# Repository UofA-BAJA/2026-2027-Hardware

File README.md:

# 2026-2027-Hardware

The repository of all hardware for 2026-2027 UofA Baja

Electrical Lead - Graham VanDerBeek

Software Lead - Karsten Yin

#### Projects:

Tachometer -

Speedometer -

Shock Displacement -

Brake Pressure -

GPS -

CVT Temp -

IMU -

Dash - Adam Esch
 HELLO

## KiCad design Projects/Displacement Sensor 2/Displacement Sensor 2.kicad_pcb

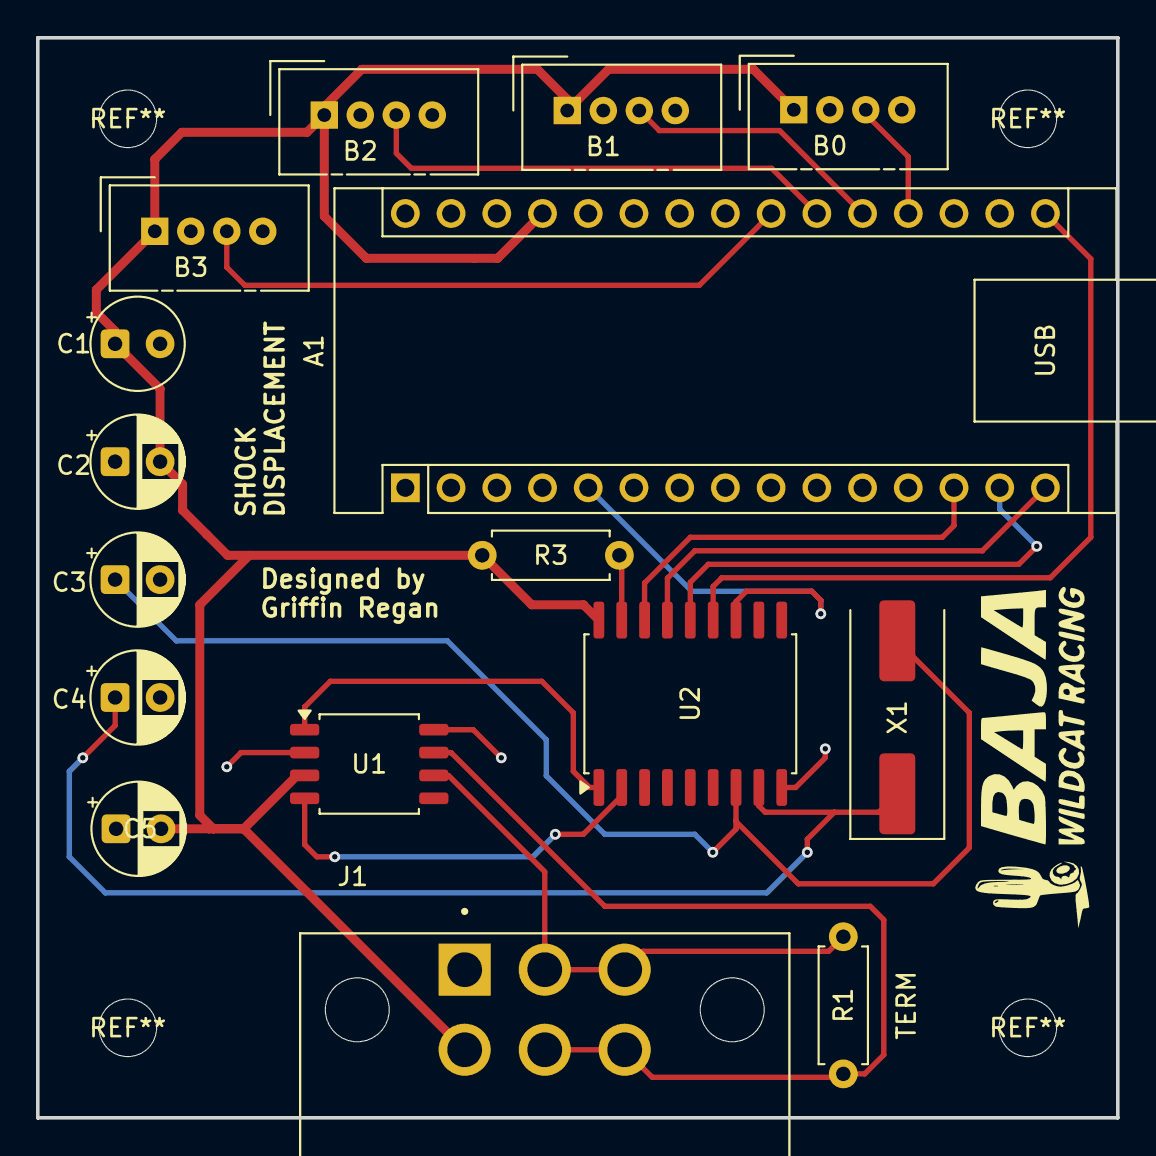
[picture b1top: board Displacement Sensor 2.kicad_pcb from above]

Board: 2 copper layers, 60.0 x 60.0 mm, 16 parts (0 on the bottom side), 18 nets.

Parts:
A1: Arduino_Nano_v3.x; Arduino_Nano
B0, B1, B2, B3: NS-Tech_Grove_1x04_P2mm_Vertical
C1: 10uF/16V; CP_Radial_Tantal_D5.0mm_P2.50mm
C2, C5: 100nF; CP_Radial_D5.0mm_P2.50mm
C3, C4: 22pF; CP_Radial_D5.0mm_P2.50mm
J1: DTF13-6P; TE_DTF13-6P
R1: TERM; R_Axial_DIN0207_L6.3mm_D2.5mm_P7.62mm_Horizontal
R3: 10k; R_Axial_DIN0207_L6.3mm_D2.5mm_P7.62mm_Horizontal
U1: TJA1050DRG; SOIC-8_5.3x5.3mm_P1.27mm
U2: MCP2515-I; SOIC-18W_7.5x11.6mm_P1.27mm
X1: 8MHz; Crystal_SMD_HC49-SD

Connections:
+5V: A1.27 (+5V), B0.1 (5V), B1.1 (5V), B2.1 (5V), B3.1 (5V), C1.1, C2.2, C5.2, J1.6, R3.1, U1.3 (VCC), U2.18 (VDD)
CS: A1.13 (D10), U2.16 (~CS)
GND: A1.4 (GND), A1.29 (GND), B0.2 (GND), B0.4 (CGND), B1.2 (GND), B1.4 (CGND), B2.2 (GND), B2.4 (CGND), B3.2 (GND), B3.4 (CGND), C1.2, C2.1, C3.2, C4.2, C5.1, J1.1, U1.2 (GND), U1.8 (STB), U2.9 (VSS)
High: J1.4, J1.5, R1.2, U1.7 (CANH)
INT: A1.5 (D2), U2.12 (~INT)
Low: J1.2, J1.3, R1.1, U1.6 (CANL)
unnamed: A1.19 (A0), B0.3 (SIGNAL)
unnamed: A1.20 (A1), B1.3 (SIGNAL)
unnamed: A1.21 (A2), B2.3 (SIGNAL)
unnamed: A1.22 (A3), B3.3 (SIGNAL)
unnamed: U1.4 (RXD), U2.2 (RXCAN)
unnamed: U1.1 (TXD), U2.1 (TXCAN)
unnamed: C4.1, U2.8 (OSC1), X1.1
unnamed: C3.1, U2.7 (OSC2), X1.2
unnamed: R3.2, U2.17 (~RESET)
SCK: A1.16 (D13), U2.13 (SCK)
SI: A1.14 (D11), U2.14 (SI)
SO: A1.15 (D12), U2.15 (SO)

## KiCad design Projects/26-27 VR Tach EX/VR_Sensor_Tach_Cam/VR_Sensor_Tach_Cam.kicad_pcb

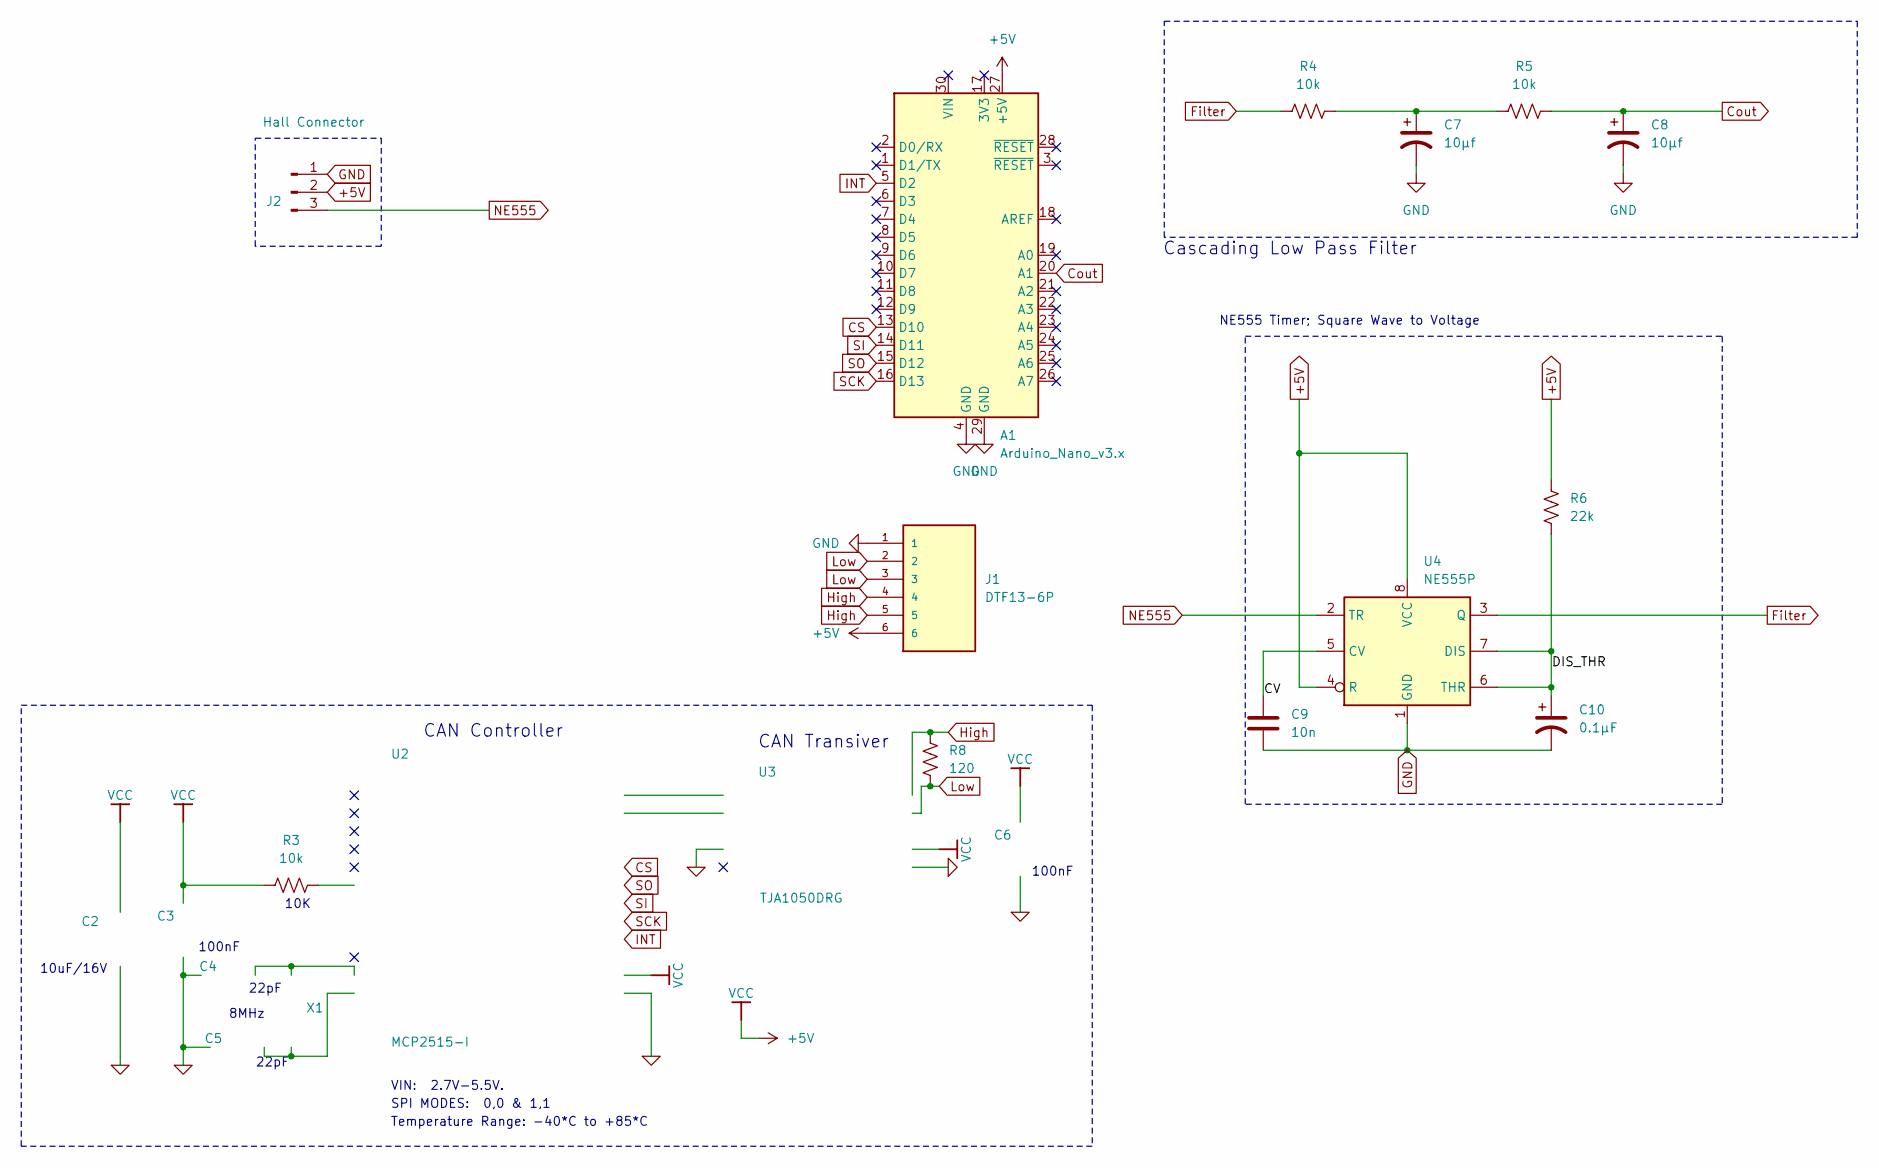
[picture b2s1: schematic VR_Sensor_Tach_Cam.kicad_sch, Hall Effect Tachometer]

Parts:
A1: Arduino_Nano_v3.x; Arduino_Nano
C2: 10uF/16V; CP_Radial_Tantal_D5.0mm_P2.50mm
C3, C6: 100nF; CP_Radial_D5.0mm_P2.50mm; PART NUMBER C0603-N.C.
C4, C5: 22pF; CP_Radial_D5.0mm_P2.50mm; PART NUMBER C0603-N.C.
C7, C8: 10μf; CP_Radial_D5.0mm_P2.50mm
C9: 10n; C_Disc_D3.8mm_W2.6mm_P2.50mm
C10: 0.1µF; CP_Radial_D6.3mm_P2.50mm
J1: DTF13-6P; TE_DTF13-6P; PARTREV B
J2: Hall Connector; SolderWire-2.5sqmm_1x03_P7.2mm_D2.4mm_OD3.6mm
R3, R4, R5: 10k; R_Axial_DIN0207_L6.3mm_D2.5mm_P10.16mm_Horizontal
R6: 22k; R_Axial_DIN0207_L6.3mm_D2.5mm_P10.16mm_Horizontal
R8: 120; R_Axial_DIN0207_L6.3mm_D2.5mm_P10.16mm_Horizontal
U2: MCP2515-I; SOIC-18W_7.5x11.6mm_P1.27mm; MANUFACTURER PART MCP2515-I; JLCPCB PART CLASS Extended Part
U3: TJA1050DRG; SOIC-8_5.3x5.3mm_P1.27mm; MANUFACTURER PART TJA1050DRG; LCSC PART NAME TJA1050DRG
U4: NE555P; DIP-8_W7.62mm
X1: 8MHz; Crystal_SMD_HC49-SD

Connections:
+5V: A1.27 (+5V), C2.1, C3.2, C6.2, J1.6, J2.2, R3.1, R6.1, U2.18 (VDD), U3.3 (VCC), U4.4 (R), U4.8 (VCC)
/CV: C9.2, U4.5 (CV)
/DIS_THR: C10.1, R6.2, U4.6 (THR), U4.7 (DIS)
CS: A1.13 (D10), U2.16 (~CS)
Cout: A1.20 (A1), C8.1, R5.1
Filter: R4.2, U4.3 (Q)
GND: A1.4 (GND), A1.29 (GND), C2.2, C3.1, C4.2, C5.2, C6.1, C7.2, C8.2, C9.1, C10.2, J1.1, J2.1, U2.9 (VSS), U3.2 (GND), U3.8 (STB), U4.1 (GND)
High: J1.4, J1.5, R8.1, U3.7 (CANH)
INT: A1.5 (D2), U2.12 (~INT)
Low: J1.2, J1.3, R8.2, U3.6 (CANL)
NE555: J2.3, U4.2 (TR)
unnamed: C7.1, R4.1, R5.2
unnamed: C5.1, U2.8 (OSC1), X1.1
unnamed: C4.1, U2.7 (OSC2), X1.2
unnamed: U2.2 (RXCAN), U3.4 (RXD)
unnamed: U2.1 (TXCAN), U3.1 (TXD)
unnamed: R3.2, U2.17 (~RESET)
SCK: A1.16 (D13), U2.13 (SCK)
SI: A1.14 (D11), U2.14 (SI)
SO: A1.15 (D12), U2.15 (SO)

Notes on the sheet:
VIN: 2.7V-5.5V.
8MHz
Cascading Low Pass Filter
10uF/16V
100nF
SPI MODES: 0,0 & 1,1
CAN Controller
CAN Transiver
10K
22pF
NE555 Timer; Square Wave to Voltage
Temperature Range: -40*C to +85*C

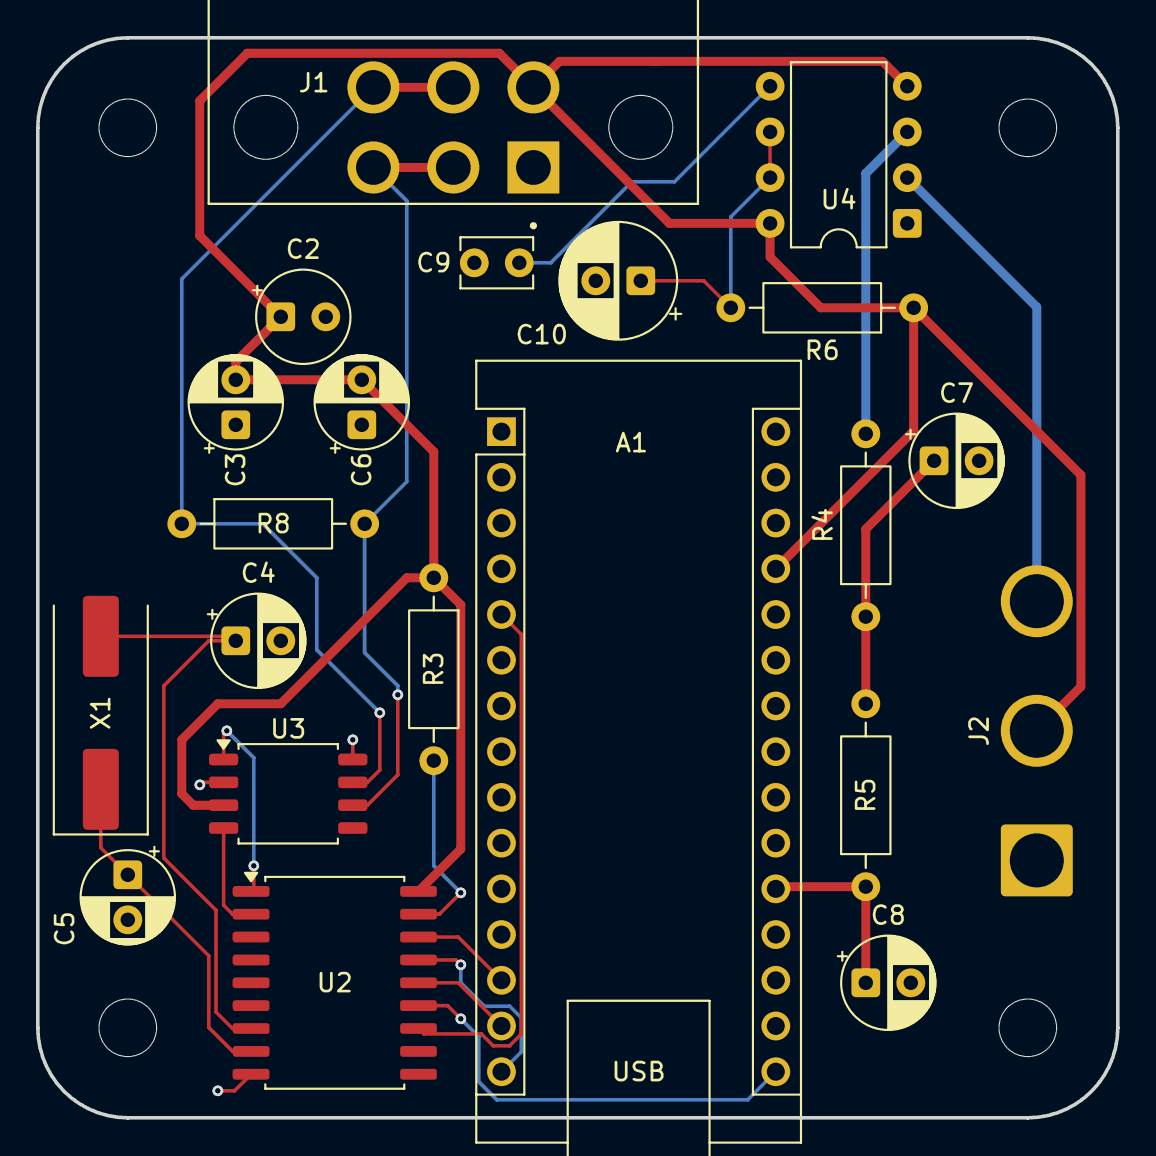
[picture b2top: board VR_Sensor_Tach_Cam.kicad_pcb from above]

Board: 2 copper layers, 60.0 x 60.0 mm, 21 parts (0 on the bottom side), 20 nets.

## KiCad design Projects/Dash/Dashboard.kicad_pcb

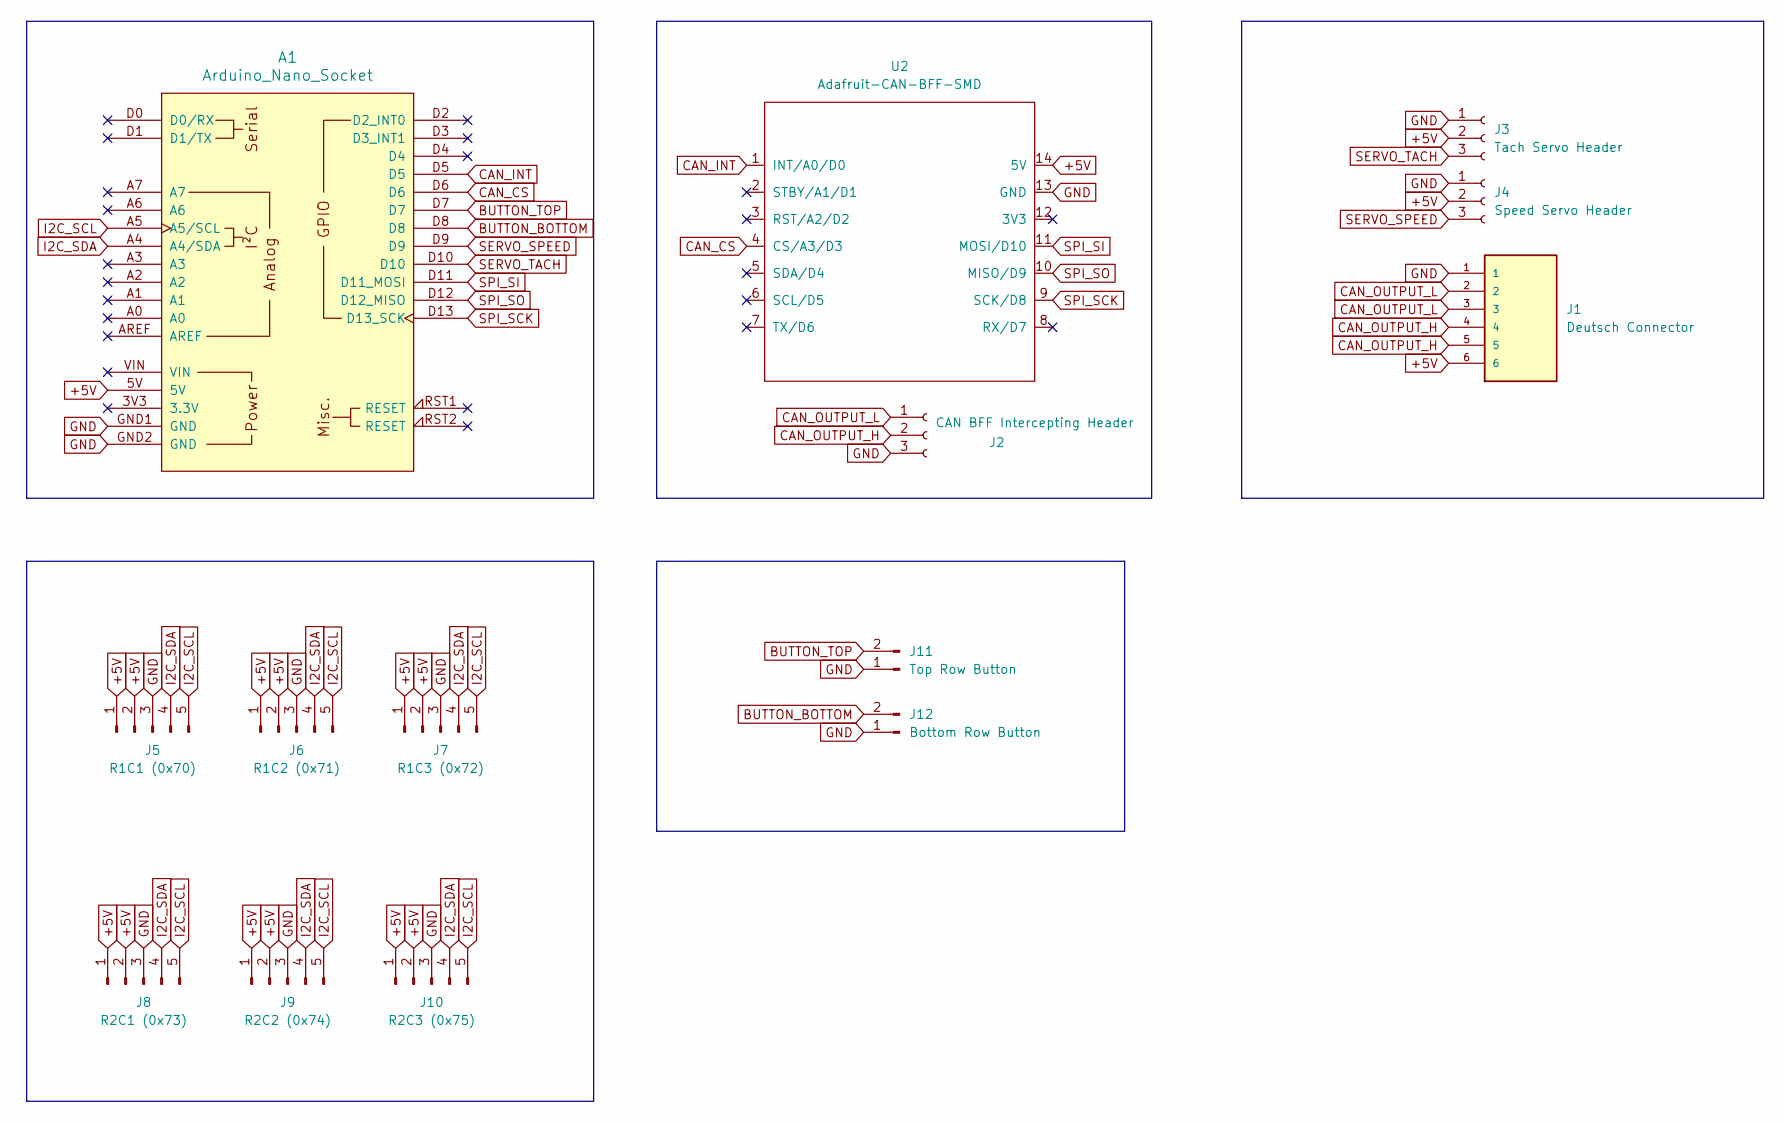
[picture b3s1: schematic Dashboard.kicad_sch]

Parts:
A1: Arduino_Nano_Socket
J1: Deutsch Connector; TE_DTF13-6P; PARTREV B
J2: CAN BFF Intercepting Header; PinHeader_1x03_P2.54mm_Vertical
J3: Tach Servo Header; PinHeader_1x03_P2.54mm_Vertical
J4: Speed Servo Header; PinHeader_1x03_P2.54mm_Vertical
J5: R1C1 (0x70); PinHeader_1x05_P2.54mm_Vertical
J6: R1C2 (0x71); PinHeader_1x05_P2.54mm_Vertical
J7: R1C3 (0x72); PinHeader_1x05_P2.54mm_Vertical
J8: R2C1 (0x73); PinHeader_1x05_P2.54mm_Vertical
J9: R2C2 (0x74); PinHeader_1x05_P2.54mm_Vertical
J10: R2C3 (0x75); PinHeader_1x05_P2.54mm_Vertical
J11: Top Row Button; PinHeader_1x02_P2.54mm_Vertical
J12: Bottom Row Button; PinHeader_1x02_P2.54mm_Vertical
U2: Adafruit-CAN-BFF-SMD

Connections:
+5V: A1.5V, J1.6, J3.2, J4.2, J5.1, J5.2, J6.1, J6.2, J7.1, J7.2, J8.1, J8.2, J9.1, J9.2, J10.1, J10.2, U2.14 (5V)
BUTTON_BOTTOM: A1.D8, J12.2
BUTTON_TOP: A1.D7, J11.2
CAN_CS: A1.D6, U2.4 (CS/A3/D3)
CAN_INT: A1.D5, U2.1 (INT/A0/D0)
CAN_OUTPUT_H: J1.4, J1.5, J2.2
CAN_OUTPUT_L: J1.2, J1.3, J2.1
GND: A1.GND1 (GND), A1.GND2 (GND), J1.1, J2.3, J3.1, J4.1, J5.3, J6.3, J7.3, J8.3, J9.3, J10.3, J11.1, J12.1, U2.13 (GND)
I2C_SCL: A1.A5 (A5/SCL), J5.5, J6.5, J7.5, J8.5, J9.5, J10.5
I2C_SDA: A1.A4 (A4/SDA), J5.4, J6.4, J7.4, J8.4, J9.4, J10.4
SERVO_SPEED: A1.D9, J4.3
SERVO_TACH: A1.D10, J3.3
SPI_SCK: A1.D13 (D13_SCK), U2.9 (SCK/D8)
SPI_SI: A1.D11 (D11_MOSI), U2.11 (MOSI/D10)
SPI_SO: A1.D12 (D12_MISO), U2.10 (MISO/D9)

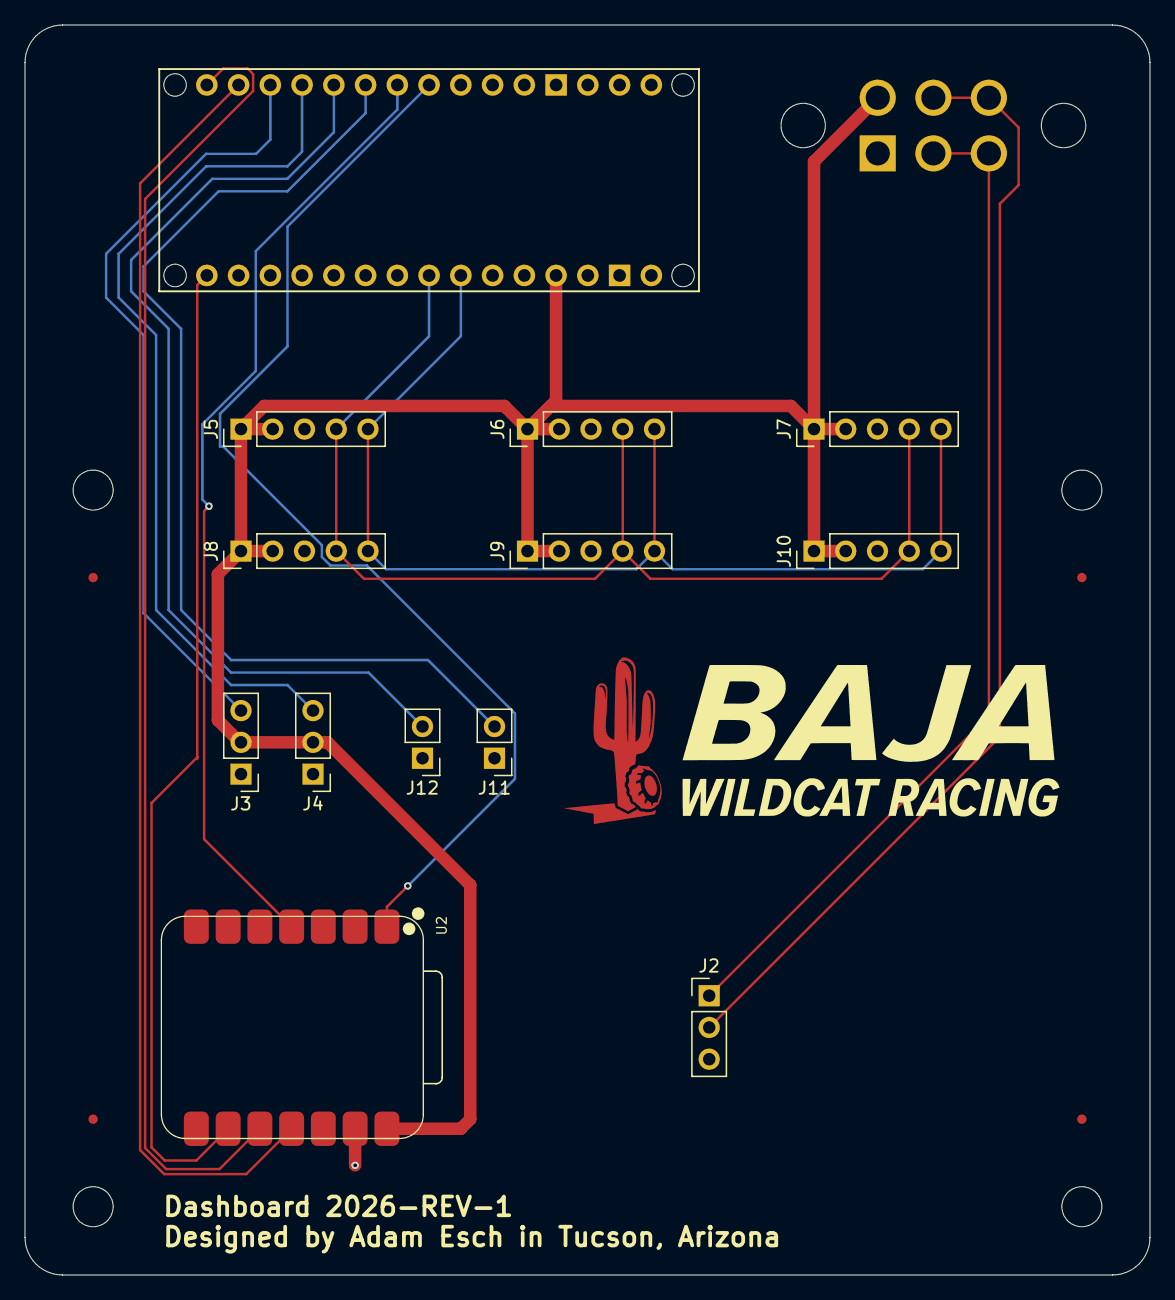
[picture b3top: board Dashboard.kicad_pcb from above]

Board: 2 copper layers, 90.0 x 100.0 mm, 14 parts (1 on the bottom side), 15 nets.

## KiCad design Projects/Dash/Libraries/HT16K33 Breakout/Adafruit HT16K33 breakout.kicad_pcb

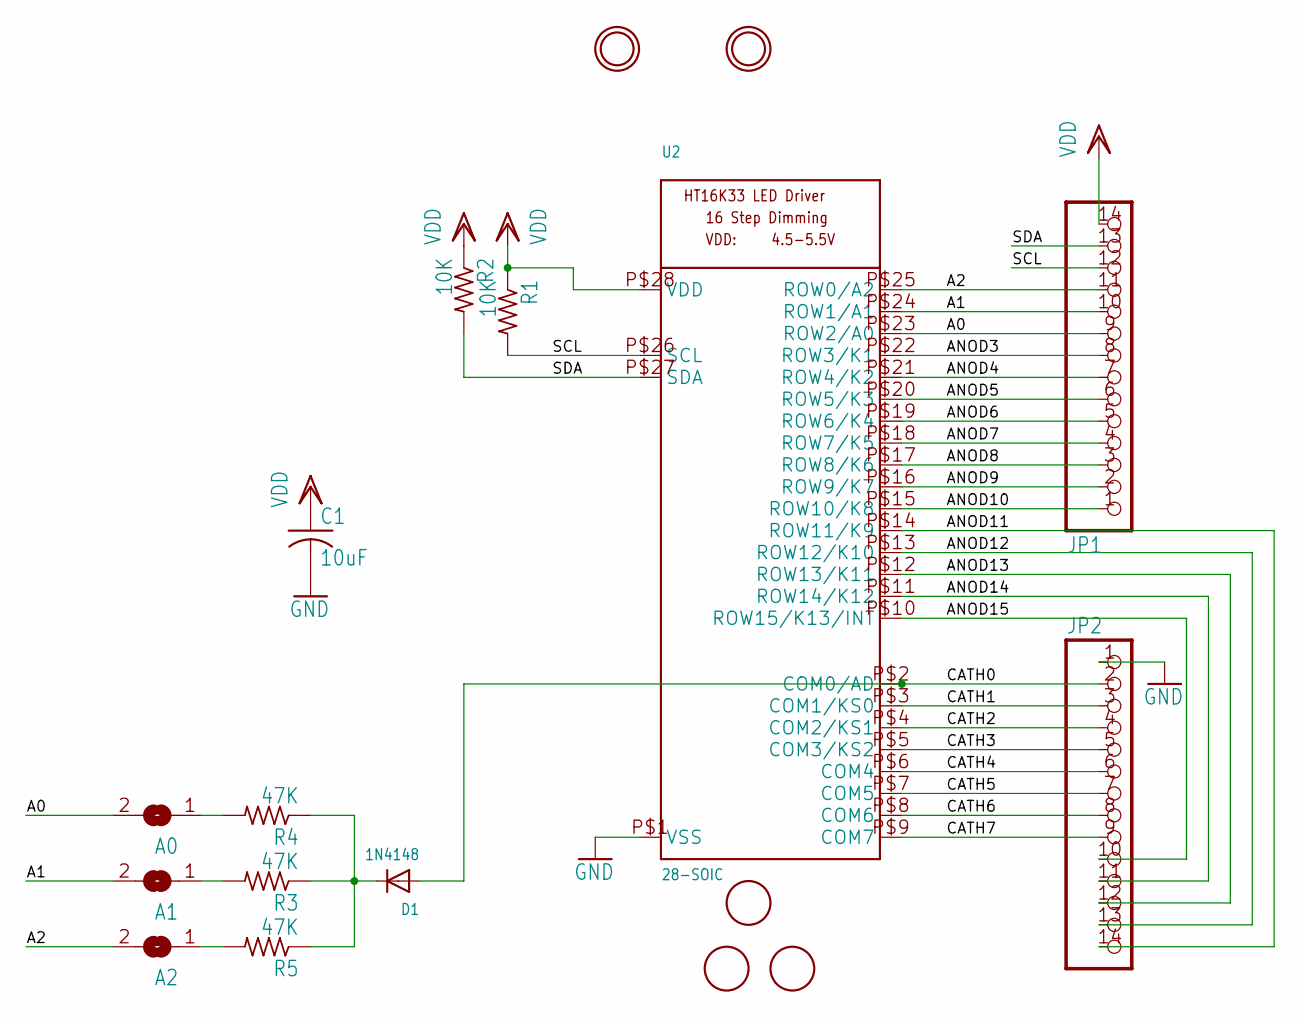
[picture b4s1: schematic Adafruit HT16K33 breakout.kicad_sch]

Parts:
A0, A1, A2: SOLDERJUMPERREFLOW_NOPASTE; SOLDERJUMPER_REFLOW_NOPASTE
C1: 10uF; C0805
D1: 1N4148; SOD-323F
JP1, JP2: PINHD-1X14-CB; 1X14-CB
R1, R2: 10K; R0805
R3, R4, R5: 47K; R0805
U2: 28-SOIC; SOP28_300MIL
U$1, U$2, U$6: FIDUCIAL; FIDUCIAL_1MM
U$4, U$5: MOUNTINGHOLE2.5; MOUNTINGHOLE_2.5_PLATED

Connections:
A0: A0.2, JP1.9, U2.P$23 (ROW2/A0)
A1: A1.2, JP1.10, U2.P$24 (ROW1/A1)
A2: A2.2, JP1.11, U2.P$25 (ROW0/A2)
ANOD3: JP1.8, U2.P$22 (ROW3/K1)
ANOD4: JP1.7, U2.P$21 (ROW4/K2)
ANOD5: JP1.6, U2.P$20 (ROW5/K3)
ANOD6: JP1.5, U2.P$19 (ROW6/K4)
ANOD7: JP1.4, U2.P$18 (ROW7/K5)
ANOD8: JP1.3, U2.P$17 (ROW8/K6)
ANOD9: JP1.2, U2.P$16 (ROW9/K7)
ANOD10: JP1.1, U2.P$15 (ROW10/K8)
ANOD11: JP2.14, U2.P$14 (ROW11/K9)
ANOD12: JP2.13, U2.P$13 (ROW12/K10)
ANOD13: JP2.12, U2.P$12 (ROW13/K11)
ANOD14: JP2.11, U2.P$11 (ROW14/K12)
ANOD15: JP2.10, U2.P$10 (ROW15/K13/INT)
CATH0: D1.A, JP2.2, U2.P$2 (COM0/AD)
CATH1: JP2.3, U2.P$3 (COM1/KS0)
CATH2: JP2.4, U2.P$4 (COM2/KS1)
CATH3: JP2.5, U2.P$5 (COM3/KS2)
CATH4: JP2.6, U2.P$6 (COM4)
CATH5: JP2.7, U2.P$7 (COM5)
CATH6: JP2.8, U2.P$8 (COM6)
CATH7: JP2.9, U2.P$9 (COM7)
GND: C1.2, JP2.1, U2.P$1 (VSS)
unnamed: A2.1, R5.2
unnamed: D1.C, R3.1, R4.1, R5.1
unnamed: A1.1, R3.2
unnamed: A0.1, R4.2
SCL: JP1.12, R1.2, U2.P$26 (SCL)
SDA: JP1.13, R2.2, U2.P$27 (SDA)
VDD: C1.1, JP1.14, R1.1, R2.1, U2.P$28 (VDD)

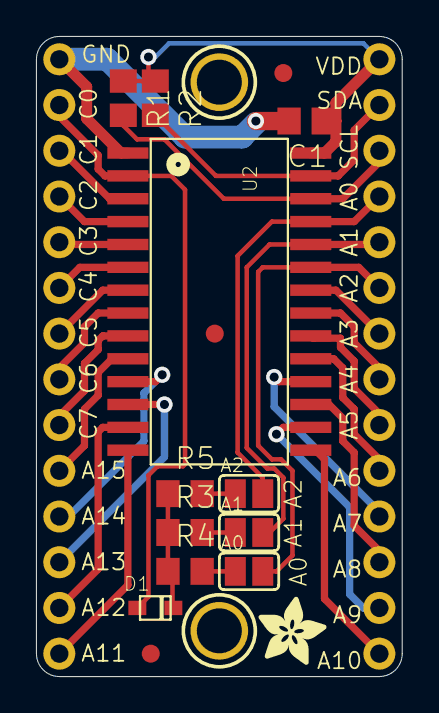
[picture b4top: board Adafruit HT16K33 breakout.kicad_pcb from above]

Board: 16 copper layers, 20.3 x 35.6 mm, 20 parts (1 on the bottom side), 32 nets.

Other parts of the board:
U$3: ADAFRUIT_3.5MM
U$7: ADAFRUIT_5MM
